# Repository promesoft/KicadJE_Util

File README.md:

# KicadJE_Util
CV utility module

# Purpose

## CV Util 1
Input +/- 10V DC

Output +/- 10V DC

Adjustment:

Inv/Noninv (input)

Offset

Gain 

## CV Util 2 - Glide
0-10V input

0-10V Output

## Gate Util 1 - Timing
0-10V input

Time shift of the start and end phase

# Status - TimeShift mounted
## Initial 
| Stage  | Detail | Status |
| ------------- | ------------- | ------------- |
| create material  | sch | ok |
| | pcb | ok |
| | gerber | ok |
| production  |   | ok |
|  | produced | ok |
|  | delivered | ok |
## Preliminary validation
| Test  | Detail | Status |
| ------------- | ------------- | ------------- |
| Initial Inspection | | ok |
| Initial Technical Test | Util | ok - but offset pots are reversed |
| Initial Technical Test | Glide | notok - CV in potential burn of output by gnd of tip |
| Initial Technical Test | TimeShift | Ok - but problem in pos/neg detection |
| Initial Product Test | Util |  |
| Initial Product Test | Glide |  |
| Initial Product Test | TimeShift |  |

## Secondary validation
| Test  | Detail | Status |
| ------------- | ------------- |------------- |
| Product Test | Util | |
| Product Test | Glide | |
| Product Test | TimeShift | |
| Quality | Util | |
| Quality | Glide | |
| Quality | TimeShift | |
| Long Term Product Test |  |  |
| Power Draw |  | 

## Errata
### Errata - 

## Issues and Notes
### 

# Pictures

# Schematic
## DC util

## Glide util

## TimeShift util

# Analysis
## Timeshift

## Prototype

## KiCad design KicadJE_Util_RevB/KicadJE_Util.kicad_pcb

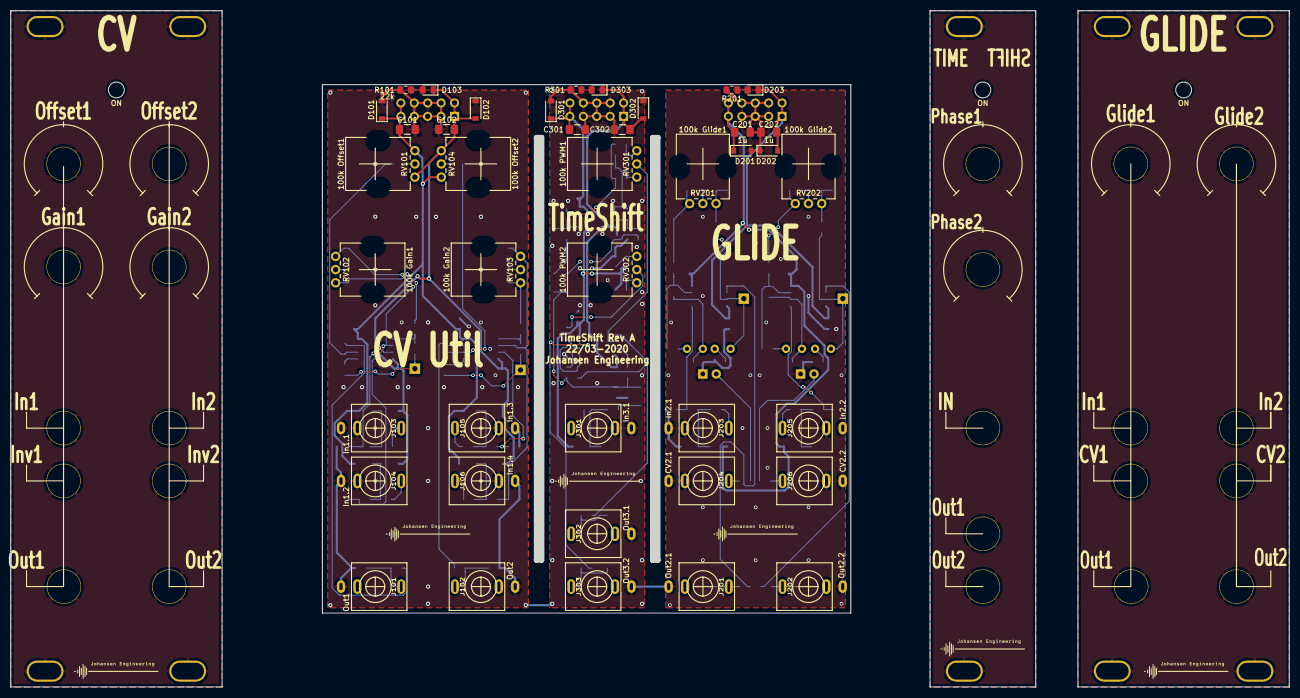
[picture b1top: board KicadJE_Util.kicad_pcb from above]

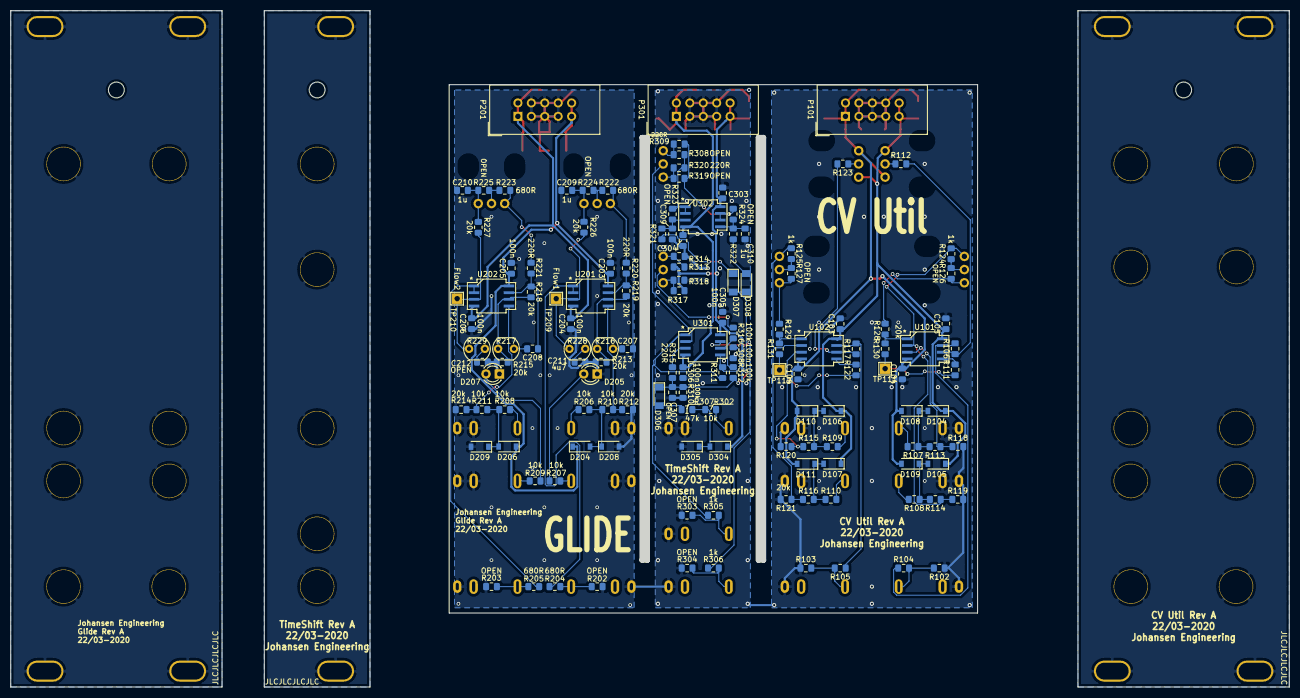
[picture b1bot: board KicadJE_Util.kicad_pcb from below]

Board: 2 copper layers, 100.0 x 100.0 mm, 212 parts (140 on the bottom side), 89 nets.

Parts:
C101, C102, C201, C202, C301, C302: 1u; C_1206_3216Metric_Pad1.42x1.75mm_HandSolder
C103, C104, C105, C106, C203, C204, C205, C206, C303, C304, C305, C306, C308: 100n; C_0805_2012Metric_Pad1.15x1.40mm_HandSolder
C207, C212, C307: OPEN; C_0805_2012Metric_Pad1.15x1.40mm_HandSolder
C208, C209, C210, C309, C310: 1u; C_0805_2012Metric_Pad1.15x1.40mm_HandSolder
C211: 4u7; C_0805_2012Metric_Pad1.15x1.40mm_HandSolder
D101, D102, D104, D105, D106, D107, D108, D109, D110, D111, D201, D202, D204, D206, D208, D209, D301, D302, D304, D305: 1N1007; D_SOD-123
D103, D203, D303: LED; LED_0805_2012Metric_Pad1.15x1.40mm_HandSolder
D205, D207: LED; LED_D3.0mm
D306, D307, D308: 1N4148; D_MiniMELF
H101, H101#2, H301: ON; LED_Hole_3mm
H102, H102#2, H102#3, H103, H103#2, H103#3, H104, H104#2, H105, H105#2: MountingHole_Pad; MountingHole_Eurorack3
J101: Out1; PJ301SM
J102: Out2; PJ301SM
J103: In1.1; PJ301SM
J104: In1.2; PJ301SM
J105: In1.3; PJ301SM
J106: In1.4; PJ301SM
J201: Out2.1; PJ301SM
J202: Out2.2; PJ301SM
J203: In2.1; PJ301SM
J204: CV2.1; PJ301SM
J205: In2.2; PJ301SM
J206: CV2.2; PJ301SM
J301: In3.1; PJ301SM
J302: Out3.1; PJ301SM
J303: Out3.2; PJ301SM
P101, P201, P301: HEADER_2x5_Doepfer; IDC-Header_2x05_P2.54mm_Vertical
R101, R201, R301: 22k; R_0805_2012Metric_Pad1.15x1.40mm_HandSolder
R102, R103, R126, R127, R202, R203, R224, R225, R303, R304, R308, R313, R318, R319, R323, R324: OPEN; R_0805_2012Metric_Pad1.15x1.40mm_HandSolder
R104, R105, R124, R125, R130, R131, R305, R306: 1k; R_0805_2012Metric_Pad1.15x1.40mm_HandSolder
R106, R117, R310, R311, R312, R316: 100k; R_0805_2012Metric_Pad1.15x1.40mm_HandSolder
R107, R108, R109, R110, R111, R112, R113, R114, R115, R116, R122, R123, R206, R207, R208, R209, R210, R211, R302: 10k; R_0805_2012Metric_Pad1.15x1.40mm_HandSolder
R118, R119, R120, R121, R128, R129, R212, R213, R214, R215, R218, R219, R226, R227, R321, R322: 20k; R_0805_2012Metric_Pad1.15x1.40mm_HandSolder
R204, R205, R222, R223: 680R; R_0805_2012Metric_Pad1.15x1.40mm_HandSolder
R216, R229: OPEN; R_LDR_5.0x4.1mm_P3mm_Vertical
R217: LDR03_In2; R_LDR_5.0x4.1mm_P3mm_Vertical
R220, R221, R309, R314, R315, R317, R320: 220R; R_0805_2012Metric_Pad1.15x1.40mm_HandSolder
R228: LDR03_In1; R_LDR_5.0x4.1mm_P3mm_Vertical
R307: 47k; R_0805_2012Metric_Pad1.15x1.40mm_HandSolder
RV101: 100k Offset1; Potentiometer_China_RK09_Single_Vertical_AJ
RV102: 100k Gain1; Potentiometer_China_RK09_Single_Vertical_AJ
RV103: 100k Gain2; Potentiometer_China_RK09_Single_Vertical_AJ
RV104: 100k Offset2; Potentiometer_China_RK09_Single_Vertical_AJ
RV201: 100k Glide1; Potentiometer_China_RK09_Single_Vertical_AJ
RV202: 100k Glide2; Potentiometer_China_RK09_Single_Vertical_AJ
RV301: 100k PWM1; Potentiometer_China_RK09_Single_Vertical_AJ
RV302: 100k PWM2; Potentiometer_China_RK09_Single_Vertical_AJ
TP102, TP102#2, TP303: SQ; Jack_6m3
TP103, TP103#2, TP301: In1; Jack_6m3
TP105, TP105#2: In3; Jack_6m3
TP106, TP106#2: HS; Jack_6m3
TP107, TP107#2, TP107#5: OFF1; Pot_6m3_scale1
TP107#3, TP107#4: FM; Jack_6m3
TP108, TP108#2: PWM; Jack_6m3
TP111, TP209: Flow1; TestPoint_THTPad_2.0x2.0mm_Drill1.0mm
TP112, TP112#2, TP112#3: Fine; Pot_6m3_scale1
TP112#4, TP210: Flow2; TestPoint_THTPad_2.0x2.0mm_Drill1.0mm
TP302: Tri; Jack_6m3
TP304: PWM1; Pot_6m3_scale1
TP305: PWM2; Pot_6m3_scale1
U101, U102, U201, U202, U301, U302: TL072; AJ_SO-8_5.3x6.2mm_P1.27mm

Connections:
+12VA: C101.1, C103.1, C105.1, C201.1, C203.1, C205.1, C301.1, C303.1, C305.1, D101.1, D104.1, D105.1, D106.1, D107.1, D201.1, D204.1, D206.1, D301.1, D304.1, P101.9, P101.10, P201.9, P201.10, P301.9, P301.10, R313.1, R317.2, RV101.1, RV104.1, U101.8, U102.8, U201.8, U202.8, U301.8, U302.8
-12VA: C102.2, C104.2, C106.2, C202.2, C204.2, C206.2, C302.2, C304.2, C306.2, D102.2, D103.1, D108.2, D109.2, D110.2, D111.2, D202.2, D203.1, D302.2, D303.1, P101.1, P101.2, P201.1, P201.2, P301.1, P301.2, RV101.3, RV104.3, U101.4, U102.4, U201.4, U202.4, U301.4, U302.4
Flow1: R111.1, R130.1, TP111.1
Flow2: R122.1, R131.1, TP112#4.1
GND: C101.2, C102.1, C103.2, C104.1, C105.2, C106.1, C201.2, C202.1, C203.2, C204.1, C205.2, C206.1, C209.2, C210.2, C211.2, C212.1, C301.2, C302.1, C303.2, C304.1, C305.2, C306.1, C307.1, C308.1, C309.1, C310.1, D101.2, D102.1, D201.2, D202.1, D205.1, D207.1, D208.2, D209.2, D301.2, D302.1, D305.2, H102.1, H102#2.1, H102#3.1, H103.1, H103#2.1, H103#3.1, H104.1, H104#2.1, H105.1, H105#2.1, J101.S, J102.S, J103.S, J103.TN, J104.S, J104.TN, J105.S, J105.TN, J106.S, J106.TN, J201.S, J202.S, J203.S, J203.TN, J204.S, J204.TN, J205.S, J205.TN, J206.S, J206.TN, J301.S, J301.TN, J302.S, J303.S, P101.3, P101.4, P101.5, P101.6, P101.7, P101.8, P201.3, P201.4, P201.5, P201.6, P201.7, P201.8, P301.3, P301.4, P301.5, P301.6, P301.7, P301.8, R101.2, R102.1, R103.1, R118.2, R119.2, R120.2, R121.2, R201.2, R202.1, R203.1, R212.2, R213.2, R214.2, R215.2, R301.2, R303.1, R304.1, R310.2, R314.1, R318.2, TP102.1, TP102#2.1, TP103.1, TP103#2.1, TP105.1, TP105#2.1, TP106.1, TP106#2.1, TP107.1, TP107#2.1, TP107#3.1, TP107#4.1, TP107#5.1, TP108.1, TP108#2.1, TP112.1, TP112#2.1, TP112#3.1, TP301.1, TP302.1, TP303.1, TP304.1, TP305.1
In1: R113.1, R118.1, U101.3
In2: R115.1, R120.1, U102.3
In2.1: R210.1, R212.1, U201.5
In2.2: R211.1, R214.1, U202.5
In3.1: D306.2, R307.1
In3.1a: C307.2, D306.1, D307.2, D308.1, R310.1, R312.1, R315.1
Inv1: R114.1, R119.1, R124.2, RV102.3, U101.2
Inv2: R116.1, R121.1, R125.2, RV103.1, U102.2
NegPk1: R309.1, R319.2, R324.1, U302.6, U302.7
unnamed: C207.1, R219.2, R220.2, U201.7
unnamed: C207.2, R216.1
unnamed: C208.1, R218.2, R221.2, U202.7
unnamed: C208.2, R217.1
unnamed: C209.1, R224.1, R226.2, RV201.1
unnamed: C210.1, R225.1, R227.1, RV202.1
unnamed: C211.1, R228.2
unnamed: C212.2, R229.1
unnamed: C308.2, R311.2, U301.5
unnamed: C309.2, R321.2, R323.2, U302.3
unnamed: C310.2, R322.2, R324.2, U302.5
unnamed: D103.2, R101.1
unnamed: D104.2, D108.1, R107.1, R113.2
unnamed: D105.2, D109.1, R108.1, R114.2
unnamed: D106.2, D110.1, R109.1, R115.2
unnamed: D107.2, D111.1, R110.1, R116.2
unnamed: D203.2, R201.1
unnamed: D204.2, D208.1, R206.1, R210.2
unnamed: D205.2, R207.1
unnamed: D206.2, D209.1, R208.1, R211.2
unnamed: D207.2, R209.1
unnamed: D303.2, R301.1
unnamed: D304.2, D305.1, R302.1, R307.2
unnamed: D307.1, R321.1
unnamed: D308.2, R322.1
unnamed: J101.T, R102.2, R104.2
unnamed: J102.T, R103.2, R105.2
unnamed: J103.T, R107.2
unnamed: J104.T, R108.2
unnamed: J105.T, R109.2
unnamed: J106.T, R110.2
unnamed: J201.T, R202.2, R204.2
unnamed: J202.T, R203.2, R205.2
unnamed: J203.T, R206.2
unnamed: J204.T, R207.2
unnamed: J205.T, R208.2
unnamed: J206.T, R209.2
unnamed: J301.T, R302.2
unnamed: J302.T, R303.2, R305.2
unnamed: J303.T, R304.2, R306.2
unnamed: R106.1, R112.2, U101.6
unnamed: R111.2, U101.5
unnamed: R112.1, RV101.2
unnamed: R117.1, R123.2, U102.6
unnamed: R122.2, U102.5
unnamed: R123.1, RV104.2
unnamed: R124.1, R126.2, RV102.2
unnamed: R125.1, R127.2, RV103.2
unnamed: R126.1, R128.1, RV102.1
unnamed: R127.1, R129.1, RV103.3
unnamed: R128.2, R130.2, U101.1
unnamed: R129.2, R131.2, U102.1
unnamed: R204.1, U201.1, U201.2
unnamed: R205.1, U202.1, U202.2
unnamed: R213.1, R216.2, R219.1, U201.6
unnamed: R215.1, R217.2, R218.1, U202.6
unnamed: R220.1, R222.2, RV201.3
unnamed: R221.1, R223.2, RV202.3
unnamed: R222.1, R224.2, RV201.2
unnamed: R223.1, R225.2, RV202.2
unnamed: R308.2, R309.2, RV301.1
unnamed: R312.2, R316.1, U301.6
unnamed: R313.2, R314.2, RV302.1
unnamed: R315.2, U301.3
unnamed: R316.2, RV302.2
unnamed: R317.1, R318.1, RV302.3
unnamed: R319.1, R320.1, RV301.3
unnamed: RV301.2, U301.2
Out1: R104.1, R106.2, U101.7
Out2: R105.1, R117.2, U102.7
Out2.1: R226.1, R228.1, TP209.1, U201.3
Out2.2: R227.2, R229.2, TP210.1, U202.3
Out3.1: R305.1, R311.1, U301.1
Out3.2: R306.1, U301.7
PosPk1: R308.1, R320.2, R323.1, U302.1, U302.2

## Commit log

2020-03-17 Initial documents
2020-03-17 Base sch done
2020-03-19 fix flow
2020-03-19 Glide initiated
2020-03-21 Update KicadJE_Util_CV2.sch
    Glide
2020-03-22 Timeshift Added
2020-03-22 Timeshift stage 1
2020-03-22 annotate
2020-03-22 PCB Cleanup and new netlist
2020-03-22 Placing IO components
2020-03-22 Update KicadJE_Timeshift_Mini.sch
    Fixing packaging of OpAmp
2020-03-22 Faceplace komp placed
2020-03-22 Update KicadJE_Util.kicad_pcb
    Time shift placed
2020-03-22 Timeshift routed
2020-03-22 CV Module placed
2020-03-22 CV Util routed - and Timeshift fixed?
2020-03-22 Labels and DRC
2020-03-22 PCB only
2020-03-22 Gerber
2020-03-22 JLC Zip
2020-04-22 RevB Initiated
2020-04-26 input changed
2020-04-29 Faceplates
2020-04-29 Generic Face Gerber
2024-12-30 attempt to go to Kicad 7
